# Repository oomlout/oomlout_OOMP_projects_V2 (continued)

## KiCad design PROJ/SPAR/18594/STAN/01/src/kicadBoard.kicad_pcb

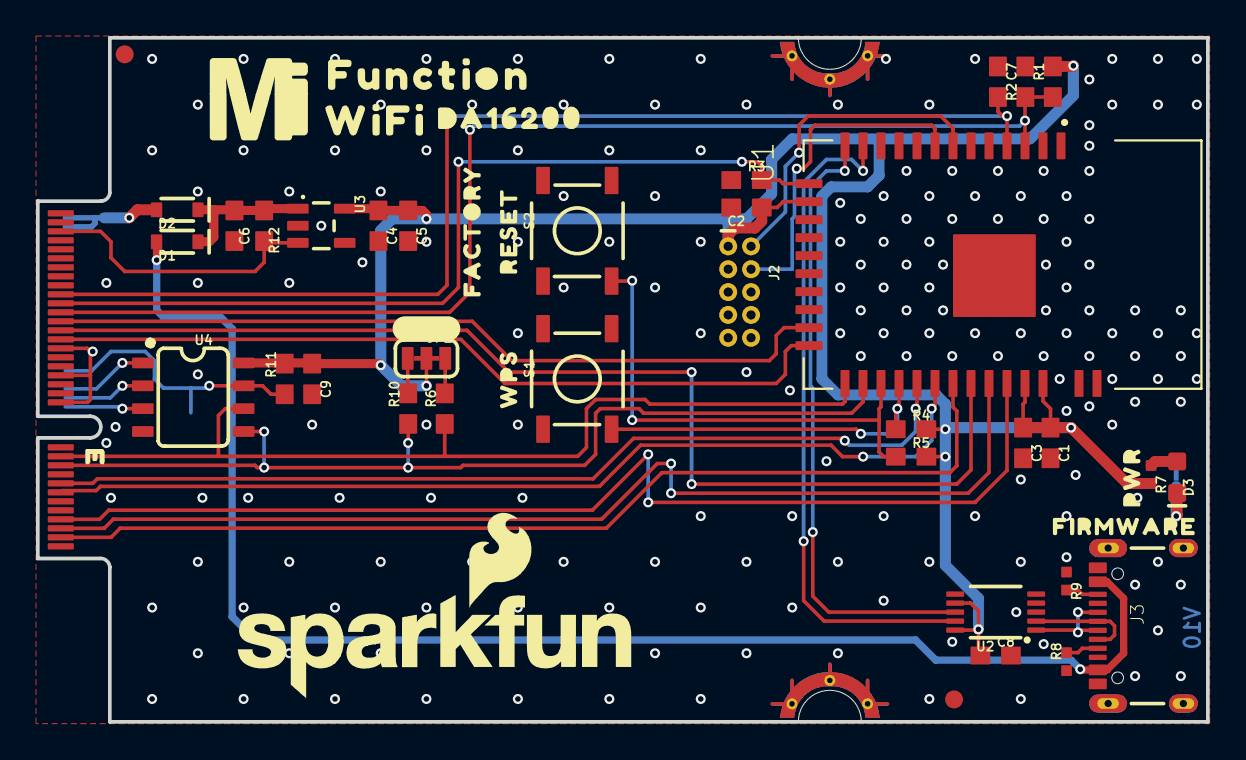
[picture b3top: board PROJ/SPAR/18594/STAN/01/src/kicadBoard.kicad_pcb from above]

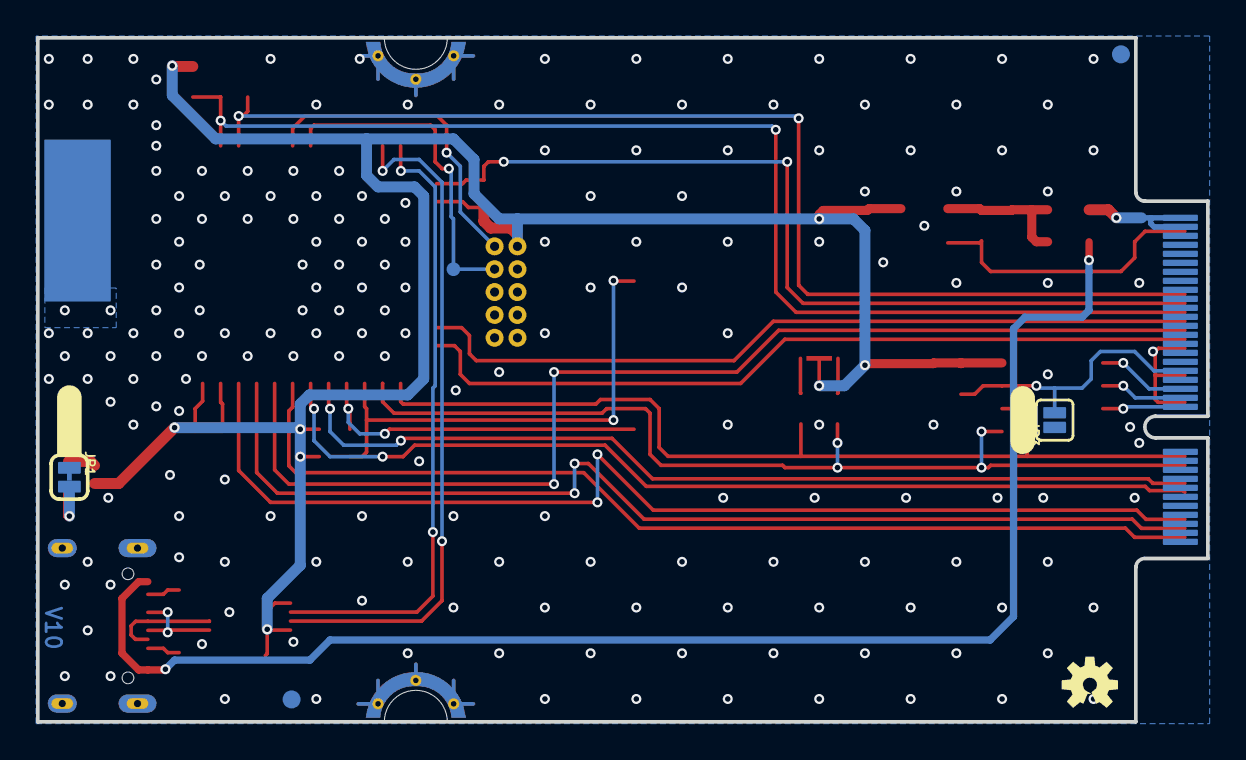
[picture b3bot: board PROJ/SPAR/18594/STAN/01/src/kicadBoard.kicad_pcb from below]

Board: 2 copper layers, 65.0 x 38.0 mm, 57 parts (8 on the bottom side), 37 nets.

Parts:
C1: 10uF; 0603
C2, C3: 1uF; 0603
C4, C6: 1.0uF; 0603
C5, C8, C9: 0.1uF; 0603
C7: DNP; 0603
D1, D2: SOD-323
D3: RED; LED-0603
FD1, FD2, FD3, FD4: FIDUCIAL1X2; FIDUCIAL-1X2
FRAME2: FRAME-LEDGER; CREATIVE_COMMONS
J1: MICROMOD_FUNCTION_STANDARD; M.2-CARD-E-22_FUNCTION_STANDARD
J2: CORTEX_JTAG_DEBUG; 2X5-PTH-1.27MM-NO_SILK
J3: USB-C-16P-2LAYER-PADS
JP1: JUMPER-SMT_2_NC_TRACE_SILK; SMT-JUMPER_2_NC_TRACE_SILK
JP2: JUMPER-SMT_3_2-NC_TRACE_SILK; SMT-JUMPER_3_2-NC_TRACE_SILK
JP3: JUMPER-SMT_2_NO_SILK; SMT-JUMPER_2_NO_SILK
LOGO1: SFE_LOGO_NAME_FLAME.2_INCH; SFE_LOGO_NAME_FLAME_.2
LOGO2: OSHW-LOGOS; OSHW-LOGO-S
LOGO3: SPECIAL_INSTRUCTIONS-ORDERING; ORDERING_INSTRUCTIONS
R1: 0603
R2, R3, R4, R5, R6, R10: 4.7k; 0603
R7: 1k; 0402-TIGHT
R8, R9: 5.1k; 0402-TIGHT
R11: 10k; 0603
R12: 100k; 0603
S1: WPS; TACTILE_SWITCH_SMD_5.2MM
S2: FACTORY_RESET; TACTILE_SWITCH_SMD_5.2MM
TP1: PAD.03X.03
U1: DA16200MOD; XCVR_DA16200MOD-AAC4WA32
U2: CH340E_MSOP10; MSOP10
U3: 3.3V; SOT23-5
U4: EEPROM; SO08
U$1: FIRMWARE0
U$2: PWR0
U$3: #LED#0
U$4: FUNCTION0
U$5: DA162000
U$6: WIFI0
U$7: WPS0
U$8: FACTORY0
U$9: RESET0
U$10: #WP#0
U$11: #I2C#0
U$12: MICROMOD_MI_LOGO_1

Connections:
3.3V: C1.1, C2.1, C3.1, C4.1, C5.1, C8.1, C9.1, J2.1, JP2.2, R1.2, R4.2, R5.2, R7.2, R11.2, U1.15, U1.34, U1.35, U2.7, U2.10, U3.5, U4.8
CIPO: J1.7, U1.33
COPI: J1.5, U1.32
EN: J1.71, R12.2, U3.3
EWP: J1.40, JP3.2, R11.1, U4.7
FACTORY_RESET: R5.1, S2.3, U1.26
GND: C1.2, C2.2, C3.2, C4.2, C5.2, C6.2, C7.2, C8.2, C9.2, J1.1, J1.33, J1.39, J1.45, J1.75, J1.GND1, J1.GND2, J1.GND3, J1.GND4, J1.GND5, J1.GND6, J2.3, J2.5, J2.9, J3.GND, J3.GND2, J3.SHLD1, J3.SHLD2, J3.SHLD3, J3.SHLD4, JP1.1, JP3.1, R2.1, R3.1, R8.1, R9.1, S1.1, S2.1, U1.2, U1.ANT_GND, U1.GND, U2.3, U3.2, U4.4
GPIOA10: J1.47, U1.23
GPIOA11: J1.51, U1.22
I2C_SCL: J1.21, R6.1, U1.24, U4.6
I2C_SDA: J1.19, R10.1, U1.25, U4.5
unnamed: J1.36, U4.1
unnamed: J3.A5, R8.2
unnamed: C6.1, D1.C, D2.C, R12.1, U3.1
unnamed: J3.B5, R9.2
unnamed: D3.C, JP1.2
unnamed: D3.A, R7.1
unnamed: J1.32, U4.3
unnamed: J1.34, U4.2
unnamed: J3.A6, J3.B6, U2.1
unnamed: J3.A7, J3.B7, U2.2
unnamed: JP2.1, R10.2
unnamed: JP2.3, R6.2
RTC_PWR_KEY: C7.1, J1.53, R1.1, U1.3
RTC_WAKE1: J1.57, R2.2, U1.4
RTC_WAKE2: J1.55, R3.2, U1.14
SCK: J1.3, U1.30
TCLK: J2.4, TP1.1, U1.8
TMS: J2.2, U1.7
U0RXI: U1.13, U2.8
U0TXO: U1.12, U2.9
U1RXI: J1.15, U1.28
U1TXO: J1.13, U1.29
VCC: D2.A, J1.72, J1.74
V_USB: D1.A, J3.VBUS1, J3.VBUS2
WPS: R4.1, S1.3, U1.27
~CS: J1.49, U1.31

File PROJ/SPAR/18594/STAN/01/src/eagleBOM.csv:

"Part";"Value";"Device";"Package";"Description";"DESIGNER";"PROD_ID";"REV";"VALUE";
"C1";"10uF";"10UF-0603-6.3V-20%";"0603";"10.0µF ceramic capacitors";"";"CAP-11015";"";"10uF";
"C2";"1uF";"1.0UF-0603-16V-10%";"0603";"1µF ceramic capacitors";"";"CAP-00868";"";"1.0uF";
"C3";"1uF";"1.0UF-0603-16V-10%";"0603";"1µF ceramic capacitors";"";"CAP-00868";"";"1.0uF";
"C4";"1.0uF";"1.0UF-0603-16V-10%";"0603";"1µF ceramic capacitors";"";"CAP-00868";"";"1.0uF";
"C5";"0.1uF";"0.1UF-0603-25V-(+80/-20%)";"0603";"0.1µF ceramic capacitors";"";"CAP-00810";"";"0.1uF";
"C6";"1.0uF";"1.0UF-0603-16V-10%";"0603";"1µF ceramic capacitors";"";"CAP-00868";"";"1.0uF";
"C7";"DNP";"CAP-0603";"0603";"";"";"";"";"";
"C8";"0.1uF";"0.1UF-0603-25V-(+80/-20%)";"0603";"0.1µF ceramic capacitors";"";"CAP-00810";"";"0.1uF";
"C9";"0.1uF";"0.1UF-0603-25V-(+80/-20%)";"0603";"0.1µF ceramic capacitors";"";"CAP-00810";"";"0.1uF";
"D1";"";"DIODE-SCHOTTKY-BAT60A";"SOD-323";"Schottky diode";"";"DIO-14072";"";"3A/10V/280mV";
"D2";"";"DIODE-SCHOTTKY-BAT60A";"SOD-323";"Schottky diode";"";"DIO-14072";"";"3A/10V/280mV";
"D3";"RED";"LED-0603_RIGHT_ANGLE";"LED-0603";"";"";"";"";"RED";
"FD1";"FIDUCIAL1X2";"FIDUCIAL1X2";"FIDUCIAL-1X2";"Fiducial Alignment Points";"";"";"";"";
"FD2";"FIDUCIAL1X2";"FIDUCIAL1X2";"FIDUCIAL-1X2";"Fiducial Alignment Points";"";"";"";"";
"FD3";"FIDUCIAL1X2";"FIDUCIAL1X2";"FIDUCIAL-1X2";"Fiducial Alignment Points";"";"";"";"";
"FD4";"FIDUCIAL1X2";"FIDUCIAL1X2";"FIDUCIAL-1X2";"Fiducial Alignment Points";"";"";"";"";
"FRAME2";"FRAME-LEDGER";"FRAME-LEDGER";"CREATIVE_COMMONS";"Schematic Frame - Ledger";"";"";"";"";
"J1";"MICROMOD_FUNCTION_STANDARD";"MICROMOD_FUNCTION_STANDARD";"M.2-CARD-E-22_FUNCTION_STANDARD";"MicroMod Connector";"";"";"";"";
"J2";"CORTEX_JTAG_DEBUG";"CORTEX_JTAG_DEBUG_PTH_NS";"2X5-PTH-1.27MM-NO_SILK";"Cortex Debug Connector - 10 pin";"";"";"";"";
"J3";"";"USB_C_2-LAYER_PADS";"USB-C-16P-2LAYER-PADS";"USB Type C 16Pin Connector";"";"CONN-14122";"";"";
"JP1";"JUMPER-SMT_2_NC_TRACE_SILK";"JUMPER-SMT_2_NC_TRACE_SILK";"SMT-JUMPER_2_NC_TRACE_SILK";"Normally closed trace jumper";"";"";"";"";
"JP2";"JUMPER-SMT_3_2-NC_TRACE_SILK";"JUMPER-SMT_3_2-NC_TRACE_SILK";"SMT-JUMPER_3_2-NC_TRACE_SILK";"Normally closed trace jumper (2 of 2 connections)";"";"";"";"";
"JP3";"JUMPER-SMT_2_NO_SILK";"JUMPER-SMT_2_NO_SILK";"SMT-JUMPER_2_NO_SILK";"Normally open jumper";"";"";"";"";
"LOGO1";"SFE_LOGO_NAME_FLAME.2_INCH";"SFE_LOGO_NAME_FLAME.2_INCH";"SFE_LOGO_NAME_FLAME_.2";"SparkFun Font Logo w/ Flame";"";"";"";"";
"LOGO2";"OSHW-LOGOS";"OSHW-LOGOS";"OSHW-LOGO-S";"Open-Source Hardware (OSHW) Logo";"";"";"";"";
"LOGO3";"SPECIAL_INSTRUCTIONS-ORDERING";"SPECIAL_INSTRUCTIONS-ORDERING";"ORDERING_INSTRUCTIONS";"Special Ordering/Production Instructions Alert";"";"";"";"";
"R1";" ";"RESISTOR0603";"0603";"Generic Resistor Package";"";" ";"";" ";
"R2";"4.7k";"4.7KOHM-0603-1/10W-1%";"0603";"4.7kΩ resistor";"";"RES-07857";"";"4.7k";
"R3";"4.7k";"4.7KOHM-0603-1/10W-1%";"0603";"4.7kΩ resistor";"";"RES-07857";"";"4.7k";
"R4";"4.7k";"4.7KOHM-0603-1/10W-1%";"0603";"4.7kΩ resistor";"";"RES-07857";"";"4.7k";
"R5";"4.7k";"4.7KOHM-0603-1/10W-1%";"0603";"4.7kΩ resistor";"";"RES-07857";"";"4.7k";
"R6";"4.7k";"4.7KOHM-0603-1/10W-1%";"0603";"4.7kΩ resistor";"";"RES-07857";"";"4.7k";
"R7";"1k";"1KOHM-0402T-1/16W-1%";"0402-TIGHT";"1kΩ resistor";"";"RES-14342";"";"1k";
"R8";"5.1k";"5.1KOHM-0402T-1/16W-1%";"0402-TIGHT";"";"";"RES-14340";"";"5.1k";
"R9";"5.1k";"5.1KOHM-0402T-1/16W-1%";"0402-TIGHT";"";"";"RES-14340";"";"5.1k";
"R10";"4.7k";"4.7KOHM-0603-1/10W-1%";"0603";"4.7kΩ resistor";"";"RES-07857";"";"4.7k";
"R11";"10k";"10KOHM-0603-1/10W-1%";"0603";"10kΩ resistor";"";"RES-00824";"";"10k";
"R12";"100k";"100KOHM-0603-1/10W-1%";"0603";"100kΩ resistor";"";"RES-07828";"";"100k";
"S1";"WPS";"MOMENTARY-SWITCH-SPST-SMD-5.2MM-TALL";"TACTILE_SWITCH_SMD_5.2MM";"Momentary Switch (Pushbutton) - SPST";"";"SWCH-14139";"";"";
"S2";"FACTORY_RESET";"MOMENTARY-SWITCH-SPST-SMD-5.2MM-TALL";"TACTILE_SWITCH_SMD_5.2MM";"Momentary Switch (Pushbutton) - SPST";"";"SWCH-14139";"";"";
"TP1";"";"TEST-POINT3";"PAD.03X.03";"SparkFun Test Points";"";"";"";"";
"U1";"DA16200MOD";"DA16200MOD-AAC4WA32";"XCVR_DA16200MOD-AAC4WA32";"Check prices";"";"IC-16179";"";"DA16200MOD";
"U2";"CH340E_MSOP10";"CH340E_MSOP10";"MSOP10";"";"";"IC-14135";"";"";
"U3";"3.3V";"V_REG_AP2112K-3.3V";"SOT23-5";"AP2112 - 600mA CMOS LDO Regulator w/ Enable";"";"VREG-12457";"";"3.3V";
"U4";"EEPROM";"EEPROM-I2C512K";"SO08";"I2C EEPROMs, 24LC256 and others";"";"IC-14645";"";"";

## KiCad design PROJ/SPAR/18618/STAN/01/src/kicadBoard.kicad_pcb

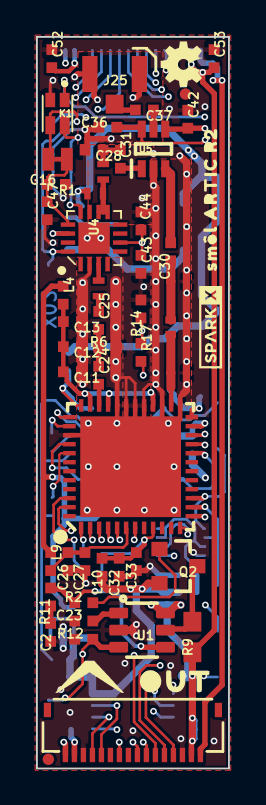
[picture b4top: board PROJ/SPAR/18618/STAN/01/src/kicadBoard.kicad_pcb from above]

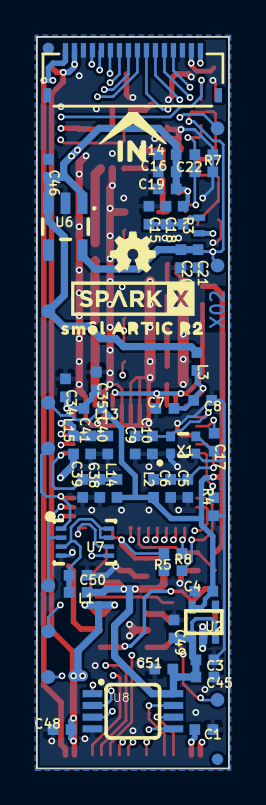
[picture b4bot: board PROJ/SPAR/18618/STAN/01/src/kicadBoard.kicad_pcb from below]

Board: 4 copper layers, 10.7 x 40.6 mm, 121 parts (64 on the bottom side), 63 nets.

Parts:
C1, C15, C16, C20, C44, C45, C48, C52, C53: 2.2uF; 0402-TIGHT
C2: 10nF; 0402-TIGHT
C3, C4, C9, C12, C23, C46: 1.0uF; 0402-TIGHT
C5, C7, C18, C27, C33, C34, C39, C40: 22pF; 0402-TIGHT
C6, C8, C26, C32, C35, C38, C41, C49, C50, C51: 0.1uF; 0402-TIGHT
C10: 47nF; 0402-TIGHT
C11, C19, C21, C22, C24, C25, C30, C31, C36, C37, C42, C43, C47: 100pF; 0402-TIGHT
C13, C14: 10uF; 0402-TIGHT
C17: 1.0nF; 0402-TIGHT
C28: 9.1pF; 0402-TIGHT
C29: 2.4 pF; 0402_MURATA
CS0: TEST-POINT3; PAD.03X.03
FD1, FD2, FD3, FD4: FIDUCIALUFIDUCIAL; FIDUCIAL-MICRO
FLSH_CEN0: TEST-POINT3; PAD.03X.03
FLSH_SCLK0: TEST-POINT3; PAD.03X.03
FLSH_SI0: TEST-POINT3; PAD.03X.03
FLSH_SO0: TEST-POINT3; PAD.03X.03
FRAME1: FRAME-LEDGER; CREATIVE_COMMONS
G16: JUMPER-SMT_2_NC_TRACE_NO-SILK; SMT-JUMPER_2_NC_TRACE_NO-SILK
GPIO0: TEST-POINT3; PAD.03X.03
IN0: FPC_16_0.5MM
J25: U.FL; U.FL_REDUCED_FOOTPRINT
K1: TLP3475SRHA
L1, L2, L3, L4, L9, L10, L13, L14, L15: 30Ω; 0402-TIGHT
L5: 15nH; 0402_COILCRAFT
L6: 27nH; 0402_COILCRAFT
L7: 18nH; 0402_COILCRAFT
L8: 12nH; 0402_COILCRAFT
L11: 30nH; 0402_COILCRAFT
L12: 51nH; 0402_COILCRAFT
LOGO1: SPECIAL_INSTRUCTIONS-ORDERING; ORDERING_INSTRUCTIONS
LOGO2, LOGO3: OSHW-LOGOMINI; OSHW-LOGO-MINI
OUT0: FPC_16_0.5MM
Q2: 5.8A/30V/35mΩ; SOT23-3
R1, R7, R12: 10k; 0402-TIGHT
R2, R11: 100; 0402-TIGHT
R3: 3.9; 0402-TIGHT
R4: 33k; 0402-TIGHT
R5, R8: 100k; 0402-TIGHT
R6: 220; 0402-TIGHT
R9: 0.1; 0603
R14: 470; 0402-TIGHT
R17: 47; 0402-TIGHT
U1: ADM4210_1TSOT6; TSOT6
U2: 1.8V/100mA; SC70
U3: ARTIC_R2; QFN-48
U4: RFPA0133; QFN50P300X300X86-17N
U5: AS179-92LF; SOT65P220X100-6N
U6: 3.0V; SOT23-5
U7: SST25VF020BUSON; USON_3X2MM
U8: PCA9536; MSOP8
U$1: OUT0
U$2, U$3: SMOL_LOGOSMALL; SMOL_SMALL
U$4: SPARKX-LOGO3; SPARKX-SMALL
U$7: IN0
U$8: SPARKX-LOGO2; SPARKX-TINY
U$9, U$10: SM�L_ARTIC_R20
UNK1V8, UNK3V0: TEST-POINT3; PAD.03X.03
VDD0: TEST-POINT3; PAD.03X.03
X1: CRYSTAL-TCXO-26MHZ; CRYSTAL-TCXO-SMD-1.65X1.25

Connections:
1.8V: C4.1, L2.2, L4.2, L9.2, L13.2, L14.2, U2.5, UNK1V8.1
3.3V: C1.1, C48.1, C52.1, C53.1, IN0.2, IN0.15, OUT0.2, OUT0.15, R9.2, U1.6
ANTENNA: C37.1, J25.FEED
BOOT: R5.1, U3.46, U8.3
CIPO: IN0.6, OUT0.6, U3.5
COPI: IN0.5, OUT0.5, U3.4
CS0: CS0.1, IN0.7, U3.2
CS1: IN0.8, OUT0.7
CS2: IN0.9, OUT0.8
FLASH_VCC: C50.1, L1.1, U7.3, U7.7, U7.8
FLSH_CEN: FLSH_CEN0.1, U3.15, U7.1
FLSH_SCLK: FLSH_SCLK0.1, U3.12, U7.6
FLSH_SI: FLSH_SI0.1, U3.13, U7.5
FLSH_SO: FLSH_SO0.1, U3.14, U7.2
G8: K1.1, U8.5
GND: C1.2, C2.2, C3.2, C4.2, C5.2, C6.2, C7.2, C8.2, C9.2, C10.2, C11.2, C12.2, C13.2, C14.2, C15.2, C16.2, C18.2, C19.2, C20.1, C21.1, C22.1, C23.2, C26.2, C27.2, C28.1, C32.2, C33.2, C34.2, C35.2, C36.2, C38.2, C39.2, C40.2, C41.2, C42.2, C43.1, C44.2, C45.2, C46.2, C47.1, C48.2, C49.2, C50.2, C51.2, C52.2, C53.2, IN0.3, IN0.14, J25.1, J25.2, K1.2, L11.P$1, L12.P$1, OUT0.3, OUT0.14, R1.2, R4.2, R6.1, R7.2, R12.2, R14.1, U1.2, U2.2, U3.25, U3.27, U3.29, U3.30, U3.31, U3.32, U3.39, U3.GND, U4.2, U4.EDAP, U5.2, U6.2, U7.4, U8.4, X1.1, X1.2
GPIO0: GPIO0.1, IN0.10, R12.1, U1.3
GPIO1: IN0.11, OUT0.10
INT1: U3.47, U8.2
unnamed: Q2.3, R9.1, U1.5
unnamed: Q2.1, R2.1
unnamed: R2.2, R11.1, U1.4
unnamed: C34.1, C35.1, L13.1, U3.24
unnamed: C40.1, C41.1, L15.1, U3.23
unnamed: C2.1, R11.2
unnamed: C23.1, U1.1
unnamed: C26.1, C27.1, L9.1, U3.6
unnamed: C32.1, C33.1, L10.1, R5.2, R8.1, U3.9
unnamed: C11.1, C12.1, C13.1, L4.1, U3.28, U3.33, U3.35
unnamed: C7.1, C8.1, L3.1, U3.36
unnamed: R4.1, U3.41
unnamed: C5.1, C6.1, L2.1, U3.40
unnamed: C9.1, C10.1, U3.37, X1.4
unnamed: C17.1, X1.3
unnamed: C17.2, U3.38
unnamed: C24.1, U3.34
unnamed: C24.2, C25.1, R6.2
unnamed: L5.P$2, U4.14
unnamed: C15.1, C18.1, L5.P$1, R3.1
unnamed: C29.P$1, L11.P$2, U3.26
unnamed: C25.2, L7.P$1
unnamed: L7.P$2, U4.3
unnamed: L6.P$2, L8.P$1, U4.9, U4.10
unnamed: C31.1, U5.1
unnamed: C30.1, U5.3
unnamed: C37.2, U5.5
unnamed: C38.1, C39.1, L14.1, U3.20
PA_PD: R17.1, U3.7
PD: C43.2, C44.1, R14.2, R17.2, U4.6
PROC_PWR_EN: IN0.1, OUT0.1
RESETB: R8.2, U3.1, U8.1
RFG8: C22.2, K1.4, R7.1, U4.12
RFG16: C47.2, G16.1, R1.1, U4.13
RF_RX: C29.P$2, C30.2, L12.P$2
RF_TX: C28.2, C31.2, L8.P$2
RXSW: C36.1, U3.22, U5.6
SCL: IN0.13, OUT0.13, U8.6
SCLK: IN0.4, OUT0.4, U3.3
SDA: IN0.12, OUT0.12, U8.7
TXSW: C42.1, U3.21, U5.4
VDD: C3.1, C14.1, C16.1, C19.1, C45.1, C46.1, C49.1, C51.1, L1.2, L3.2, L6.P$1, L10.2, L15.2, Q2.2, R3.2, U2.1, U2.3, U6.1, U6.3, U8.8, VDD0.1
VREF1: C20.2, C21.2, G16.2, K1.3, U4.16, U6.5, UNK3V0.1
V_USB: IN0.16, OUT0.16

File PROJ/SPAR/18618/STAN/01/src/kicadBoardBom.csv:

"Id";"Designator";"Package";"Quantity";"Designation";"Supplier and ref";
1;"C52,C53,C44,C45,C16,C48,C1,C15,C20";"0402-TIGHT";9;"2.2uF";;;
2;"C37,C43,C30,C36,C11,C47,C24,C31,C25,C42,C21,C19,C22";"0402-TIGHT";13;"100pF";;;
3;"R14";"0402-TIGHT";1;"470";;;
4;"U1";"TSOT6";1;"ADM4210_1TSOT6";;;
5;"L7";"0402_COILCRAFT";1;"18nH";;;
6;"FD1,FD3,FD4,FD2";"FIDUCIAL-MICRO";4;"FIDUCIALUFIDUCIAL";;;
7;"J25";"U.FL_REDUCED_FOOTPRINT";1;"U.FL";;;
8;"U$9,U$10";"SM�L_ARTIC_R20";2;"";;;
9;"C26,C32,C8,C51,C50,C38,C35,C41,C6,C49";"0402-TIGHT";10;"0.1uF";;;
10;"FRAME1";"CREATIVE_COMMONS";1;"FRAME-LEDGER";;;
11;"R2,R11";"0402-TIGHT";2;"100";;;
12;"U$2,U$3";"SMOL_SMALL";2;"SMOL_LOGOSMALL";;;
13;"C29";"0402_MURATA";1;"2.4 pF";;;
14;"L6";"0402_COILCRAFT";1;"27nH";;;
15;"L12";"0402_COILCRAFT";1;"51nH";;;
16;"C23,C12,C3,C46,C4,C9";"0402-TIGHT";6;"1.0uF";;;
17;"L4,L9,L10,L3,L13,L2,L15,L14,L1";"0402-TIGHT";9;"30Ω";;;
18;"OUT0,IN0";"FPC_16_0.5MM";2;"";;;
19;"R6";"0402-TIGHT";1;"220";;;
20;"C33,C27,C40,C39,C7,C5,C18,C34";"0402-TIGHT";8;"22pF";;;
21;"G16";"SMT-JUMPER_2_NC_TRACE_NO-SILK";1;"JUMPER-SMT_2_NC_TRACE_NO-SILK";;;
22;"C2";"0402-TIGHT";1;"10nF";;;
23;"U5";"SOT65P220X100-6N";1;"AS179-92LF";;;
24;"U4";"QFN50P300X300X86-17N";1;"RFPA0133";;;
25;"U3";"QFN-48";1;"ARTIC_R2";;;
26;"R12,R1,R7";"0402-TIGHT";3;"10k";;;
27;"U$1";"OUT0";1;"";;;
28;"L8";"0402_COILCRAFT";1;"12nH";;;
29;"Q2";"SOT23-3";1;"5.8A/30V/35mΩ";;;
30;"R17";"0402-TIGHT";1;"47";;;
31;"C28";"0402-TIGHT";1;"9.1pF";;;
32;"L11";"0402_COILCRAFT";1;"30nH";;;
33;"K1";"TLP3475SRHA";1;"TLP3475SRHA";;;
34;"C13,C14";"0402-TIGHT";2;"10uF";;;
35;"U$8";"SPARKX-TINY";1;"SPARKX-LOGO2";;;
36;"R9";"0603";1;"0.1";;;
37;"LOGO1";"ORDERING_INSTRUCTIONS";1;"SPECIAL_INSTRUCTIONS-ORDERING";;;
38;"LOGO2,LOGO3";"OSHW-LOGO-MINI";2;"OSHW-LOGOMINI";;;
39;"U$4";"SPARKX-SMALL";1;"SPARKX-LOGO3";;;
40;"VDD0,FLSH_SO0,FLSH_SI0,UNK1V8,UNK3V0,CS0,GPIO0,FLSH_SCLK0,FLSH_CEN0";"PAD.03X.03";9;"TEST-POINT3";;;
41;"R3";"0402-TIGHT";1;"3.9";;;
42;"U7";"USON_3X2MM";1;"SST25VF020BUSON";;;
43;"C10";"0402-TIGHT";1;"47nF";;;
44;"U2";"SC70";1;"1.8V/100mA";;;
45;"L5";"0402_COILCRAFT";1;"15nH";;;
46;"U8";"MSOP8";1;"PCA9536";;;
47;"U$7";"IN0";1;"";;;
48;"X1";"CRYSTAL-TCXO-SMD-1.65X1.25";1;"CRYSTAL-TCXO-26MHZ";;;
49;"R4";"0402-TIGHT";1;"33k";;;
50;"C17";"0402-TIGHT";1;"1.0nF";;;
51;"R5,R8";"0402-TIGHT";2;"100k";;;
52;"U6";"SOT23-5";1;"3.0V";;;

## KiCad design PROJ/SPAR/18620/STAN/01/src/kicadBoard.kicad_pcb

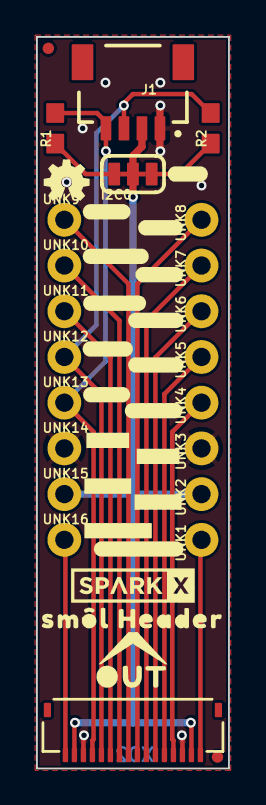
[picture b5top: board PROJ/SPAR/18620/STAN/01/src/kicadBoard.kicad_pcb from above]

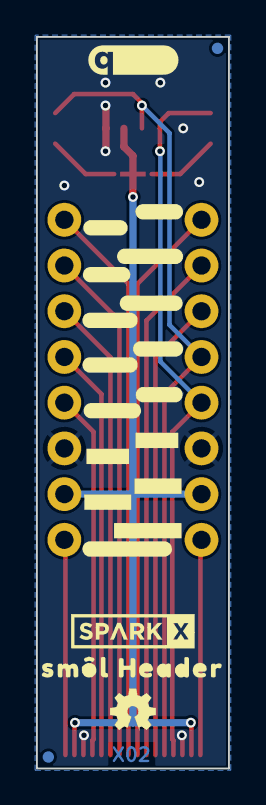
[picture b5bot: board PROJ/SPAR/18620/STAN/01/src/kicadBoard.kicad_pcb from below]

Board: 2 copper layers, 10.7 x 40.6 mm, 69 parts (22 on the bottom side), 16 nets.

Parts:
FD1, FD2, FD3, FD4: FIDUCIALUFIDUCIAL; FIDUCIAL-MICRO
FRAME1: FRAME-LEDGER; CREATIVE_COMMONS
I2C0: JUMPER-SMT_3_2-NC_TRACE_SILK; SMT-JUMPER_3_2-NC_TRACE_SILK
J1: QWIIC_RIGHT_ANGLE; JST04_1MM_RA
LOGO1: SPECIAL_INSTRUCTIONS-ORDERING; ORDERING_INSTRUCTIONS
LOGO2, LOGO3: OSHW-LOGOMINI; OSHW-LOGO-MINI
LOGO4: QWIIC_LOGO_5MM; QWIIC_5MM
OUT0: FPC_16_0.5MM
R1, R2: 2.2k; 0603
U$1, U$20: SPARKX-LOGO3; SPARKX-SMALL
U$2, U$4, U$23, U$24: #3#3V#0
U$3, U$22: #V_USB#0
U$5, U$25: #PWR_EN#0
U$6, U$7, U$26, U$27: #GND#0
U$8, U$28: #SCLK#0
U$9, U$38: #SCL#0
U$10, U$29: #COPI#0
U$11, U$30: #SDA#0
U$12, U$31: #CIPO#0
U$13, U$21: SM�L_HEADER0
U$14, U$32: #GPIO1#0
U$15, U$33: #CS0#0
U$16, U$34: #GPIO0#0
U$17, U$35: #CS1#0
U$18, U$36: #CS2#0
U$19: #I�C#0
U$37: OUT0
U$39: SMOL_LOGOSMALL; SMOL_SMALL
UNK1, UNK2, UNK3, UNK4, UNK5, UNK6, UNK7, UNK8, UNK9, UNK10, UNK11, UNK12, UNK13, UNK14, UNK15, UNK16: 1X01_NO_SILK

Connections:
3.3V: I2C0.2, J1.2, OUT0.2, OUT0.15, UNK2.1, UNK15.1
CIPO: OUT0.6, UNK6.1
COPI: OUT0.5, UNK5.1
CS0: OUT0.7, UNK7.1
CS1: OUT0.8, UNK8.1
CS2: OUT0.9, UNK9.1
GND: J1.1, OUT0.3, OUT0.14, UNK3.1, UNK14.1
GPIO0: OUT0.10, UNK10.1
GPIO1: OUT0.11, UNK11.1
unnamed: I2C0.3, R1.2
unnamed: I2C0.1, R2.2
PROC_PWR_EN: OUT0.1, UNK1.1
SCL: J1.4, OUT0.13, R1.1, UNK13.1
SCLK: OUT0.4, UNK4.1
SDA: J1.3, OUT0.12, R2.1, UNK12.1
V_USB: OUT0.16, UNK16.1

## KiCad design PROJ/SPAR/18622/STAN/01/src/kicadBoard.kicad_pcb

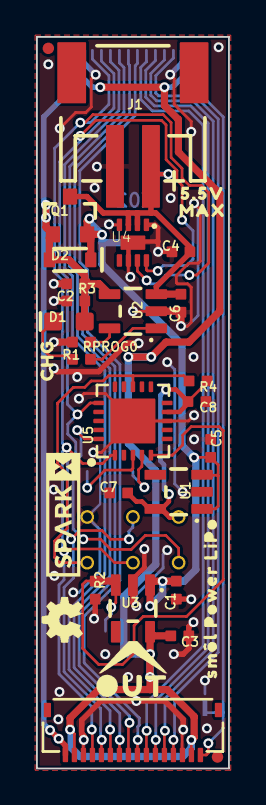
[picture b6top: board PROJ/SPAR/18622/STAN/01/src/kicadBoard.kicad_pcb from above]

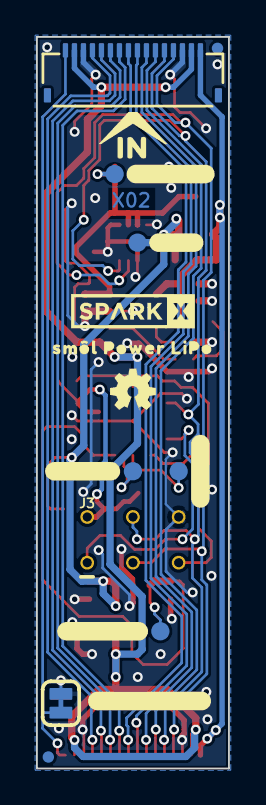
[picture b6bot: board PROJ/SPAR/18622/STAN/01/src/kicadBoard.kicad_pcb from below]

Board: 2 copper layers, 10.7 x 40.6 mm, 56 parts (21 on the bottom side), 25 nets.

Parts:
BATT+0: TEST-POINT3X4; PAD.03X.04
C1, C2, C3, C5, C7: 2.2uF; 0402-TIGHT
C4, C8: 0.1uF; 0402-TIGHT
C6: 4.7uF; 0402-TIGHT
D1: Yellow; LED-0603
D2: 1A/23V/620mV; SOD-323
FD1, FD2, FD3, FD4: FIDUCIALUFIDUCIAL; FIDUCIAL-MICRO
FRAME1: FRAME-LEDGER; CREATIVE_COMMONS
IN0: FPC_16_0.5MM
J1: JST-2-SMD
J3: AVR_SPI_PROG_3X2TESTPOINTS; 2X3_TEST_POINTS
LOGO1: SPECIAL_INSTRUCTIONS-ORDERING; ORDERING_INSTRUCTIONS
LOGO2, LOGO3: OSHW-LOGOMINI; OSHW-LOGO-MINI
OUT0: FPC_16_0.5MM
PROC_PWR_EN0: JUMPER-SMT_2_NC_TRACE_SILK; SMT-JUMPER_2_NC_TRACE_SILK
Q1: 3.1A/30V/105mΩ; SOT23-3
R1: 1k; 0402-TIGHT
R2, R3: 100k; 0402-TIGHT
R4: 4.7k; 0402-TIGHT
RPROG0: 10k; 0402-TIGHT
RXD0: TEST-POINT3X4; PAD.03X.04
TXD0: TEST-POINT3X4; PAD.03X.04
U1: STLQ015-3.3V; SOT23-5
U2: MCP73831; SOT23-5
U3: 3.3V; SOT23-5
U4: MAX17048; DFN-8
U5: ATTINY841-ARDUINO_QFN20M1; QFN20_20M1
U$1, U$20: SPARKX-LOGO3; SPARKX-SMALL
U$2, U$18: SM�L_POWER_LIPO0
U$3, U$9: SMOL_LOGOSMALL; SMOL_SMALL
U$4: #BATT##0
U$5: #VIN#0
U$6: #3V3_EN#0
U$7: #PROC_PWR#0
U$8: IN0
U$10: CHG0
U$11: MAX0
U$14: #RXD0#0
U$15: #TXD0#0
U$16: 5#5V0
U$17: OUT0
UNK3V3_EN0: TEST-POINT3X4; PAD.03X.04
VIN0: TEST-POINT3X4; PAD.03X.04

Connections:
3.3V: C3.1, IN0.2, IN0.15, OUT0.2, OUT0.15, U3.5
3V3_EN: R2.2, U3.3, U5.5, UNK3V3_EN0.1
AT_CIPO: J3.1, U5.20
AT_VCC: C7.1, C8.1, J3.2, R4.2, U1.5, U5.9
CHG_LED: R1.1, U2.1
CIPO: IN0.6, OUT0.6
COPI: IN0.5, OUT0.5
CS0: IN0.7, OUT0.7
CS1: IN0.8, OUT0.8
CS2: IN0.9, OUT0.9
GND: C1.2, C2.2, C3.2, C4.2, C5.2, C6.2, C7.2, C8.2, IN0.3, IN0.14, J1.1, J3.6, OUT0.3, OUT0.14, PROC_PWR_EN0.2, R2.1, R3.1, RPROG0.1, U1.2, U2.2, U3.2, U4.1, U4.4, U4.6, U4.9, U5.8, U5.PAD
GPIO0: IN0.10, OUT0.10
GPIO1: IN0.11, OUT0.11
unnamed: RPROG0.2, U2.5
unnamed: D1.C, R1.2
PROC_PWR_EN: IN0.1, OUT0.1, PROC_PWR_EN0.1
RXD0: RXD0.1, U5.3
SCL: IN0.13, J3.3, OUT0.13, U4.7, U5.1
SCLK: IN0.4, OUT0.4
SDA: IN0.12, J3.4, OUT0.12, U4.8, U5.16
TXD0: TXD0.1, U5.4
VIN: C1.1, C5.1, D2.C, Q1.2, U1.1, U1.3, U3.1, VIN0.1
V_BATT: BATT+0.1, C4.1, C6.1, J1.2, Q1.3, U2.3, U4.2, U4.3
V_USB: C2.1, D1.A, D2.A, IN0.16, OUT0.16, Q1.1, R3.2, U2.4
~RESET: J3.5, R4.1, U5.13

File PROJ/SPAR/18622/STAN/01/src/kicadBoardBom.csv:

"Id";"Designator";"Package";"Quantity";"Designation";"Supplier and ref";
1;"U$16";"5#5V0";1;"";;;
2;"U5";"QFN20_20M1";1;"ATTINY841-ARDUINO_QFN20M1";;;
3;"C4,C8";"0402-TIGHT";2;"0.1uF";;;
4;"R4";"0402-TIGHT";1;"4.7k";;;
5;"C2,C3,C1,C5,C7";"0402-TIGHT";5;"2.2uF";;;
6;"C6";"0402-TIGHT";1;"4.7uF";;;
7;"R3,R2";"0402-TIGHT";2;"100k";;;
8;"FRAME1";"CREATIVE_COMMONS";1;"FRAME-LEDGER";;;
9;"U3";"SOT23-5";1;"3.3V";;;
10;"D2";"SOD-323";1;"1A/23V/620mV";;;
11;"U2";"SOT23-5";1;"MCP73831";;;
12;"OUT0,IN0";"FPC_16_0.5MM";2;"";;;
13;"U$10";"CHG0";1;"";;;
14;"J1";"JST-2-SMD";1;"";;;
15;"D1";"LED-0603";1;"Yellow";;;
16;"LOGO1";"ORDERING_INSTRUCTIONS";1;"SPECIAL_INSTRUCTIONS-ORDERING";;;
17;"LOGO2,LOGO3";"OSHW-LOGO-MINI";2;"OSHW-LOGOMINI";;;
18;"FD1,FD3,FD2,FD4";"FIDUCIAL-MICRO";4;"FIDUCIALUFIDUCIAL";;;
19;"U$17";"OUT0";1;"";;;
20;"U1";"SOT23-5";1;"STLQ015-3.3V";;;
21;"U$3,U$9";"SMOL_SMALL";2;"SMOL_LOGOSMALL";;;
22;"U$1,U$20";"SPARKX-SMALL";2;"SPARKX-LOGO3";;;
23;"R1";"0402-TIGHT";1;"1k";;;
24;"U4";"DFN-8";1;"MAX17048";;;
25;"Q1";"SOT23-3";1;"3.1A/30V/105mΩ";;;
26;"U$18,U$2";"SM�L_POWER_LIPO0";2;"";;;
27;"RPROG0";"0402-TIGHT";1;"10k";;;
28;"U$11";"MAX0";1;"";;;
29;"UNK3V3_EN0,BATT+0,TXD0,VIN0,RXD0";"PAD.03X.04";5;"TEST-POINT3X4";;;
30;"U$5";"#VIN#0";1;"";;;
31;"U$14";"#RXD0#0";1;"";;;
32;"J3";"2X3_TEST_POINTS";1;"AVR_SPI_PROG_3X2TESTPOINTS";;;
33;"U$4";"#BATT##0";1;"";;;
34;"PROC_PWR_EN0";"SMT-JUMPER_2_NC_TRACE_SILK";1;"JUMPER-SMT_2_NC_TRACE_SILK";;;
35;"U$15";"#TXD0#0";1;"";;;
36;"U$6";"#3V3_EN#0";1;"";;;
37;"U$8";"IN0";1;"";;;
38;"U$7";"#PROC_PWR#0";1;"";;;

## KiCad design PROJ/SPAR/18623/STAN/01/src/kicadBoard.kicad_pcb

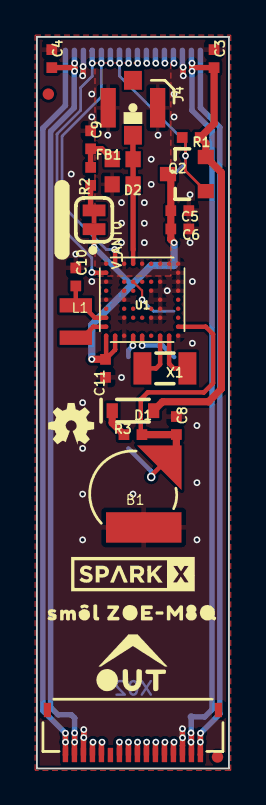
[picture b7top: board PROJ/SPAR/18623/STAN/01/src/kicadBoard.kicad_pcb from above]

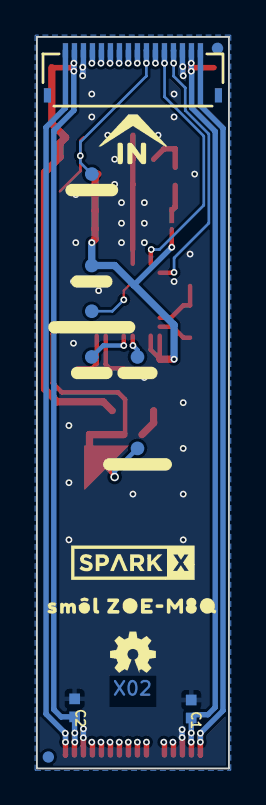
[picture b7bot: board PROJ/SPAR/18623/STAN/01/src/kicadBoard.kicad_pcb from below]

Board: 4 copper layers, 10.7 x 40.6 mm, 54 parts (22 on the bottom side), 27 nets.

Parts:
!SAFEBOOT!0: TEST-POINT3; PAD.03X.03
B1: 6.8MM_COIN_CELL; ML414H_IV01E
C1, C2, C3, C4, C5: 2.2uF; 0402-TIGHT
C6, C11: 0.1uF; 0402-TIGHT
C8: 1.0uF; 0402-TIGHT
C9: 47PF-0402_TIGHT-25V-5%-X7R; 0402-TIGHT
C10: 4.7uF; 0402-TIGHT
D1: 1A/23V/620mV; SOD-323
D2: PESD0402; 0402
FB1: FERRITE_BEAD-120_OHM-0402; 0402
FD1, FD2, FD3, FD4: FIDUCIALUFIDUCIAL; FIDUCIAL-MICRO
FRAME1: FRAME-LEDGER; CREATIVE_COMMONS
GPIO0: TEST-POINT3; PAD.03X.03
IN0: FPC_16_0.5MM
J4: U.FL
L1: 2.2uH; 0806
LOGO1: SPECIAL_INSTRUCTIONS-ORDERING; ORDERING_INSTRUCTIONS
LOGO2, LOGO3: OSHW-LOGOMINI; OSHW-LOGO-MINI
OUT0: FPC_16_0.5MM
Q2: 20V/4.2A/52mΩ/1.4W; SOT23-3
R1: 100k; 0402-TIGHT
R2: 2; 0402-TIGHT
R3: 1k; 0402-TIGHT
RXD0: TEST-POINT3; PAD.03X.03
TXD0: TEST-POINT3; PAD.03X.03
U1: U-BLOX_ZOE_M8Q-0-10; UBLOX_ZOE_M8-0-10
U$1, U$4: SPARKX-LOGO3; SPARKX-SMALL
U$2, U$12: SM�L_ZOE#M8Q0
U$3, U$13: SMOL_LOGOSMALL; SMOL_SMALL
U$5: #V_ANT#0
U$6: #VDD#0
U$7: ##SAFEBOOT##0
U$8: #TXD#0
U$9: #RXD#0
U$10: #GPIO0#0
U$11: #V_BCKP#0
U$14: OUT0
U$15: IN0
VDD0: TEST-POINT3; PAD.03X.03
V_ANT0: JUMPER-SMT_2_NC_TRACE_SILK; SMT-JUMPER_2_NC_TRACE_SILK
V_BCKP0: TEST-POINT3; PAD.03X.03
X1: 32.768kHz; CRYSTAL-SMD-3.2X1.5MM

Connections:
3.3V: C1.1, C2.1, C3.1, C4.1, D1.A, IN0.2, IN0.15, OUT0.2, OUT0.15, Q2.2, R1.2
ANT: D2.2, FB1.1, J4.FEED, U1.4
CIPO: IN0.6, OUT0.6
COPI: IN0.5, OUT0.5
CS0: IN0.7, OUT0.7
CS1: IN0.8, OUT0.8
CS2: IN0.9, OUT0.9
GND: B1.-, C1.2, C2.2, C3.2, C4.2, C5.2, C6.2, C8.2, C9.2, C10.2, C11.2, D2.1, IN0.3, IN0.14, J4.1, J4.2, OUT0.3, OUT0.14, U1.1, U1.3, U1.5, U1.7, U1.8, U1.9, U1.10, U1.11, U1.12, U1.17, U1.23, U1.29, U1.31, U1.37, U1.38, U1.39, U1.40, U1.41, U1.44, U1.46, U1.47, U1.49
GPIO0: GPIO0.1, IN0.10, Q2.1, R1.1
GPIO1: IN0.11, OUT0.10
unnamed: R2.2, V_ANT0.1
unnamed: D1.C, R3.2
unnamed: L1.2, U1.26
unnamed: C10.1, L1.1, U1.27
unnamed: U1.18, X1.P$2
unnamed: U1.19, X1.P$1
unnamed: C9.1, FB1.2, R2.1
PROC_PWR_EN: IN0.1, OUT0.1
RXD: RXD0.1, U1.22
SCL: IN0.13, OUT0.13, U1.32
SCLK: IN0.4, OUT0.4
SDA: IN0.12, OUT0.12, U1.2
TXD: TXD0.1, U1.21
VDD: C5.1, C6.1, C11.1, Q2.3, U1.24, U1.25, VDD0.1, V_ANT0.2
V_BCKP: B1.+, C8.1, R3.1, U1.16, V_BCKP0.1
V_USB: IN0.16, OUT0.16
~SAFEBOOT: !SAFEBOOT!0.1, U1.34

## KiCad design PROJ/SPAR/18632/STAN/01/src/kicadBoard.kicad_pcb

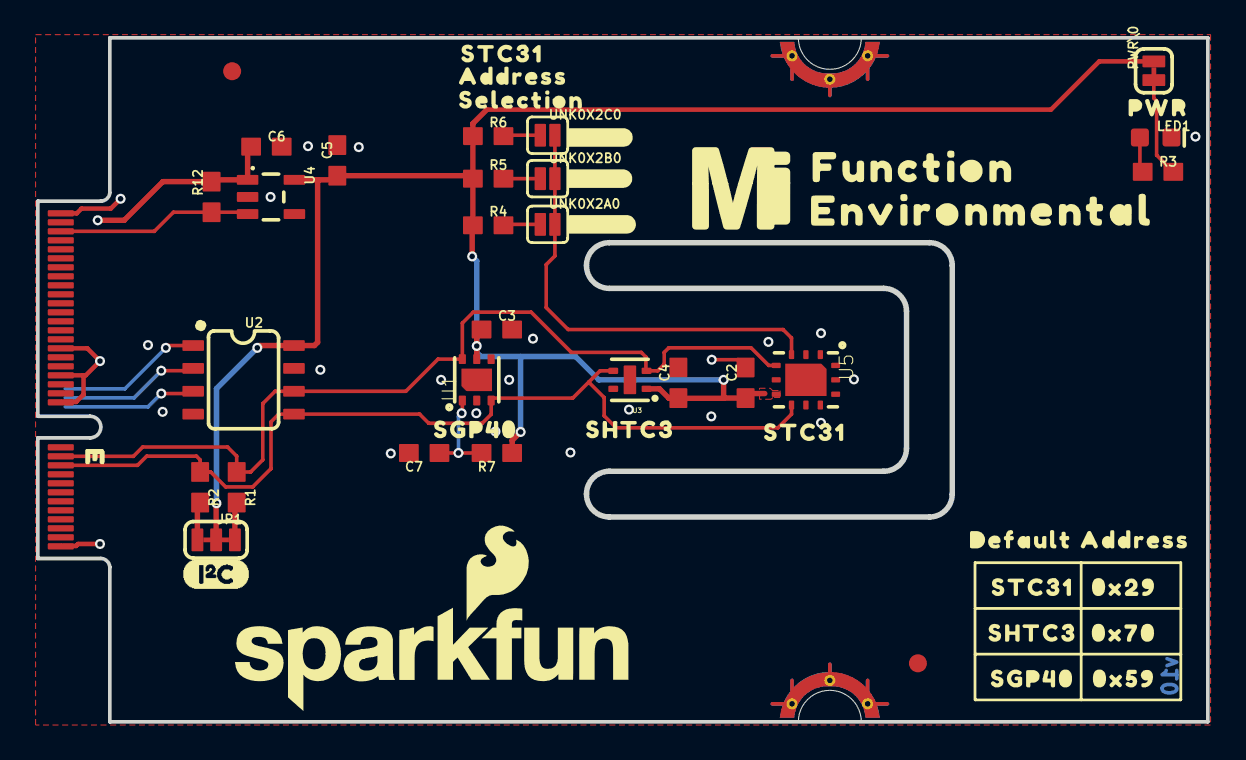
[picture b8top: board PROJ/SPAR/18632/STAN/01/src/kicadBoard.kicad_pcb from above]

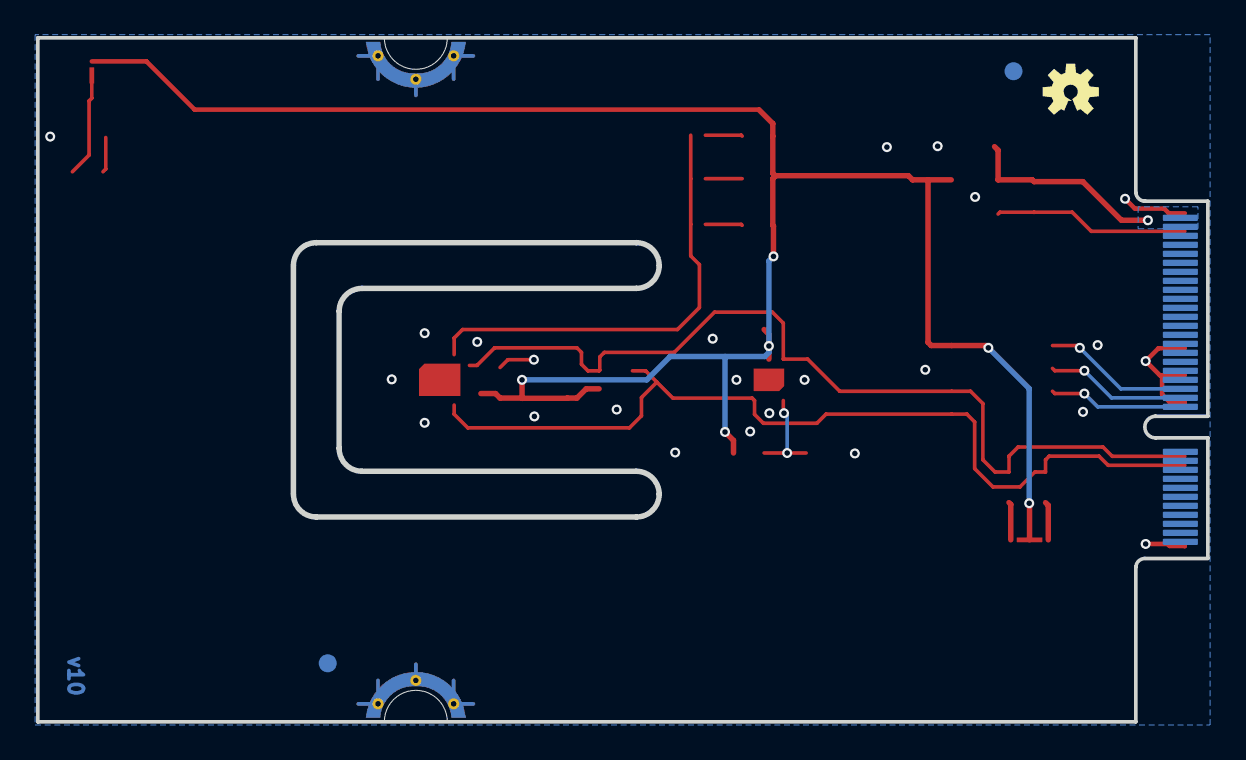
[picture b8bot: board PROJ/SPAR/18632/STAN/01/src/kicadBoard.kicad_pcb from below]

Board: 2 copper layers, 65.0 x 38.0 mm, 56 parts (3 on the bottom side), 18 nets.

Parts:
C2, C5, C6, C7: 1.0uF; 0603
C3, C4: 0.1uF; 0603
FD1, FD2, FD3, FD4: FIDUCIAL1X2; FIDUCIAL-1X2
FRAME1: FRAME-LEDGER; CREATIVE_COMMONS
J1: MICROMOD_FUNCTION_STANDARD; M.2-CARD-E-22_FUNCTION_STANDARD
JP1: JUMPER-SMT_3_2-NC_TRACE_SILK; SMT-JUMPER_3_2-NC_TRACE_SILK
LED1: RED; LED-0603
LOGO1: SFE_LOGO_NAME_FLAME.2_INCH; SFE_LOGO_NAME_FLAME_.2
LOGO2: OSHW-LOGOS; OSHW-LOGO-S
LOGO3: SPECIAL_INSTRUCTIONS-ORDERING; ORDERING_INSTRUCTIONS
PWR\0: JUMPER-SMT_2_NC_TRACE_SILK; SMT-JUMPER_2_NC_TRACE_SILK
R1, R2: 4.7k; 0603
R3, R6: 1k; 0603
R4: 10k; 0603
R5: 3.3k; 0603
R7: 4.7; 0603
R12: 100k; 0603
U1: SGP40
U2: EEPROM; SO08
U3: SHTC3
U4: 3.3V; SOT23-5
U5: STC31
U$1: #0X2A#21
U$2: #0X2B#21
U$3: #0X2C#21
U$4: PWR321541
U$5: FUNCTION524
U$6: ENVIRONMENTAL526
U$7: MICROMOD_MI_LOGO_1
U$8: I2C
U$9, U$15: ADDRESS40313505
U$10: 0X2940313520
U$11, U$18: SGP40313503
U$12, U$17: SHTC3501
U$13, U$16, U$22: STC313502
U$14: DEFAULT40313504
U$19: 0X5940313520
U$20: 0X7040313520
U$21: SELECTION40313506
UNK0X2A0, UNK0X2B0, UNK0X2C0: JUMPER-SMT_2_NO_SILK; SMT-JUMPER_2_NO_SILK

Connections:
3.3V: C2.1, C3.1, C4.1, C5.1, JP1.2, PWR\0.2, R4.1, R5.1, R6.1, R7.1, U1.5, U2.8, U3.1, U4.5, U5.6
A0: J1.36, U2.1
A1: J1.34, U2.2
A2: J1.32, U2.3
ADDR: U5.3, UNK0X2A0.2, UNK0X2B0.2, UNK0X2C0.2
EN: J1.71, R12.1, U4.3
GND: C2.2, C3.2, C4.2, C5.2, C6.2, C7.2, J1.1, J1.33, J1.39, J1.45, J1.75, J1.GND1, J1.GND2, J1.GND3, J1.GND4, J1.GND5, J1.GND6, LED1.C, U1.2, U1.4, U1.DIEPAD, U2.4, U2.7, U3.4, U3.5, U4.2, U5.1, U5.5, U5.9, U5.11, U5.DIEPAD
unnamed: PWR\0.1, R3.2
unnamed: C7.1, R7.2, U1.1
unnamed: JP1.3, R1.2
unnamed: JP1.1, R2.2
unnamed: R4.2, UNK0X2A0.1
unnamed: R5.2, UNK0X2B0.1
unnamed: R6.2, UNK0X2C0.1
unnamed: LED1.A, R3.1
SCL: J1.21, R1.1, U1.6, U2.6, U3.2, U5.4
SDA: J1.19, R2.1, U1.3, U2.5, U3.3, U5.7
VCC: C6.1, J1.72, J1.74, R12.2, U4.1
